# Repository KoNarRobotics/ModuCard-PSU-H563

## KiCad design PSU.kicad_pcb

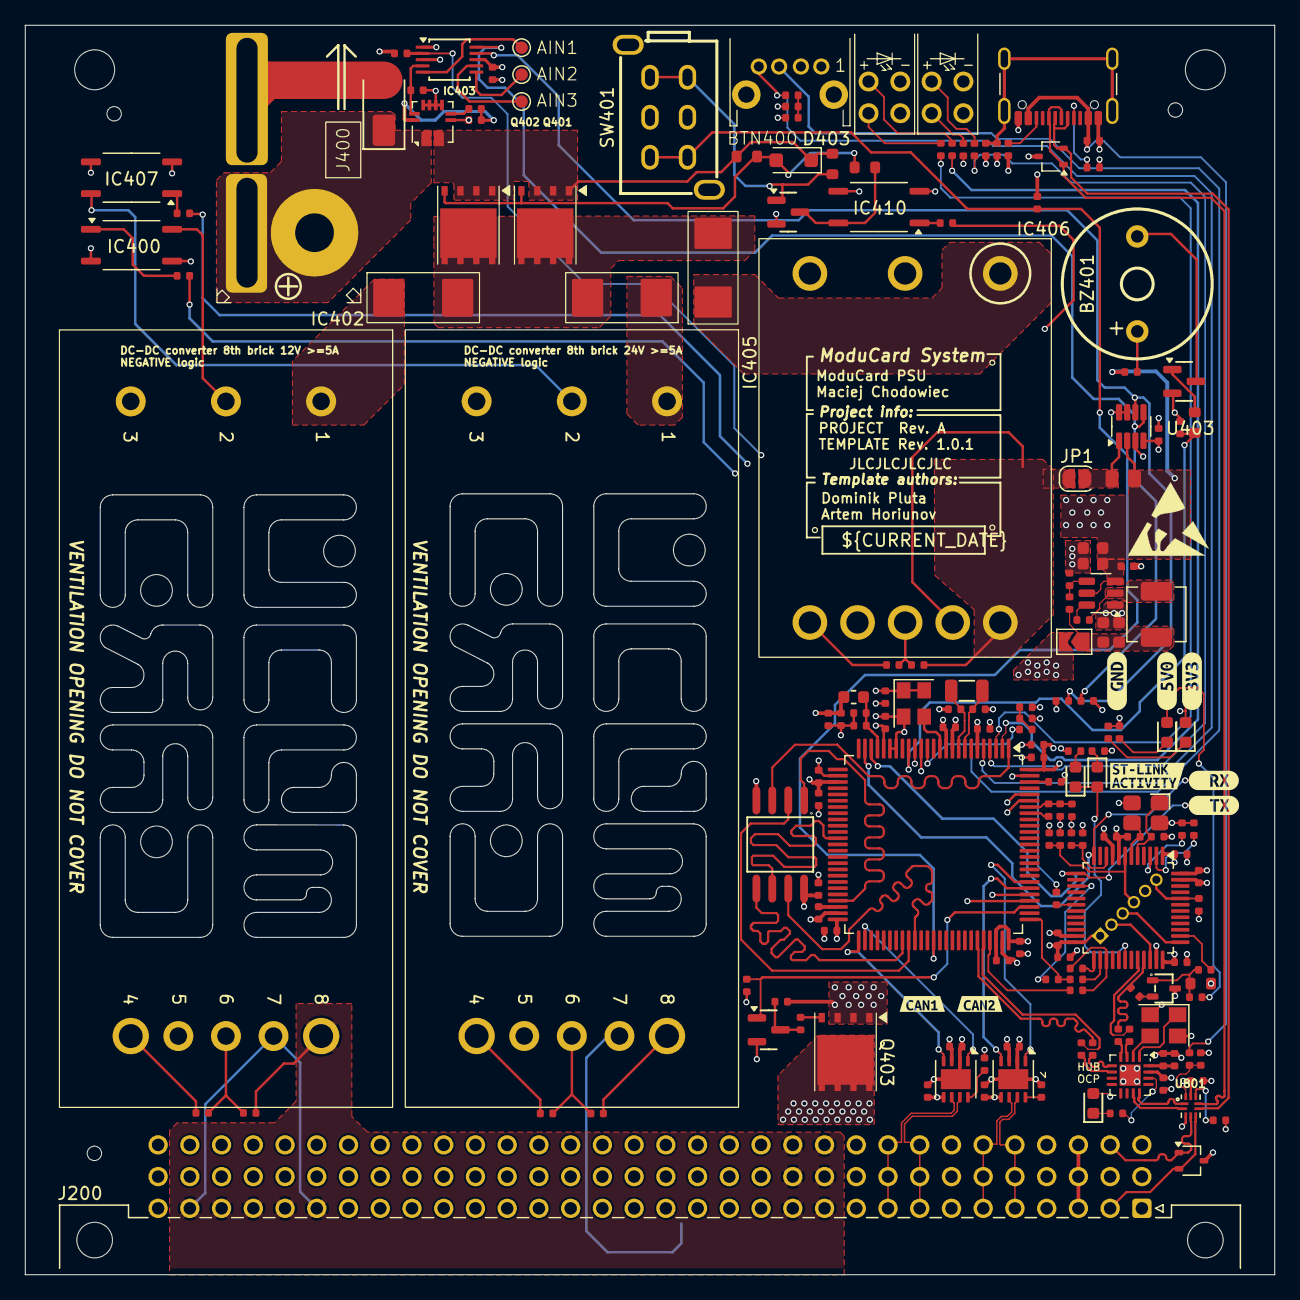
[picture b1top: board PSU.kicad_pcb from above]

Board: 4 copper layers, 100.0 x 100.0 mm, 187 parts (1 on the bottom side), 134 nets.

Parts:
BTN400: TL2243
BZ401: Buzzer; BUZ-TH_BD12.0-P7.60-D0.6-FD
C100, C306, C311, C312, C401, C402, C404, C405, C406, C417, C418, C419, C420, C421, C422, C424, C426, C428, C430, C432, C434, C500, C501, C600, C601, C701, C702, C703, C704, C705, C706, C800, C801, C900: 100nF; C_0402
C307, C308: 22uF; C_0603
C309, C310: 10uF; C_0603
C313, C314: 18pF; C_0402
C400, C403, C423, C425, C902: 10uF; C_0402
C410: 4.7uF; C_0402
C427, C429: 2.2uF; C_0402
C700, C904: 1uF; C_0402
C707, C708: 33pF; C_0402
D301: Red; D_0603
D401, D402, D701: Green; D_0603
D403: 20V; D_SOD-123F
D404: SMAJ64A; D_SMA
D700: Blue; D_0603
F402, F403, F404: 10A; Fuse_2410_6125
FB401: FB_0603
IC400, IC407, IC410: TLP185xSE; SOIC-4_4.55x3.7mm_P2.54mm
IC402, IC405: 8th DC-DC converter
IC403: ACS71240; Allegro_QFN-12-10-1EP_3x3mm_P0.5mm
IC406: 16th DC-DC converter
J200: 09031967921; DIN41612_R_3x32_Female_Horizontal_THT
J400: XT60-Angled-F; XT60-RightAngle-Adapter
J401: Conn_01x06_Pin; PinHeader_1x06_P1.27mm_Vertical
J800: USB_C_Receptacle_USB2.0_16P; USB_C_Receptacle_GCT_USB4105-xx-A_16P_TopMnt_Horizontal
JP1: Solder Jumper; SolderJumper-2_P1.3mm_Open_RoundedPad1.0x1.5mm
JP301: Test Buck Vout; SolderJumper-2_P1.3mm_Open_TrianglePad1.0x1.5mm
L301: 3.3uH; L_Changjiang_FXL0420
LED300, LED301: FixLed307
Q400, Q404: AO3400A; Q_SOT-23
Q401, Q402, Q403: HSBA8119; DFN5060-8L
Q405: MMBT5551; Q_SOT-23
Q700: MMST3904; Q_SOT-323
R306: 33k2; R_0402
R307, R401, R402, R410, R422, R423, R428, R429, R434, R435, R439, R500, R600, R701, R703, R705, R706, R707, R709, R713, R802, R804: 10kΩ; R_0402
R308, R413, R418, R437: 1kΩ; R_0402
R400: 15kΩ; R_0603
R403: 100kΩ; R_0603
R404: 36kΩ; R_0603
R411: 470Ω; R_0402
R412, R417, R440, R441, R442, R443: 220Ω; R_0402
R414, R700, R702: 100kΩ; R_0402
R415: 5.1kΩ; R_0603
R416: 100Ω; R_0603
R419: 8mΩ; R_0805
R420, R421, R424, R425, R426, R427: R; R_0402
R430, R704, R708, R715, R716, R900, R901, R902, R903: 22Ω; R_0402
R436, R438, R710, R714: 100Ω; R_0402
R445: 120Ω; R_0402
R712: 1.5kΩ; R_0402
R800, R801: 5.1kΩ; R_0402
R803: 22kΩ; R_0402
R805: 330Ω; R_0402
SW401: SW-TH_G-SWITCH-PS-22F03N
TP302, TP400, TP401, TP402, TP700, TP701: TestPoint; TestPoint_Pad_D1.0mm
U100: W25Q128; SOIC-8_L5.3-W5.3-P1.27-LS8.0-BL
U301: TPS563201DDCR; SOT-23-6
U302: CH334P; QFN-16-1EP_3x3mm_P0.5mm_EP1.7x1.7mm
U401, U402: TPD2E2U06DCK; SOT-323_SC-70
U403: INA219AIDCNR; SOT-23-8
U404: ADS1115IDGS; TSSOP-10_3x3mm_P0.5mm
U405: STM32H562VGTx; LQFP-100_14x14mm_P0.5mm
U500, U600: TJA1044GTK_3Z; HVSON-8-1EP_3x3mm_P0.65mm_EP1.6x2.4mm
U700: STM32F103CBTx; LQFP-48_7x7mm_P0.5mm
U801: FSUSB42UMX; UFQFN-10_1.4x1.8
X300: Q13FC1350000400; FC-135R_L3.2-W1.5
Y400: ASE-xxxMHz; Oscillator_SMD_Abracon_ASE-4Pin_3.2x2.5mm
Y700: 8 MHz; CRYSTAL-SMD_4P-L3.2-W2.5-BL
Y900: 12Mhz; Crystal_SMD_3225-4Pin_3.2x2.5mm
kibuzzard-67B20BD5: G***; kibuzzard-67B20BD5
kibuzzard-67B219C6: G***; kibuzzard-67B219C6
kibuzzard-67B643DE: G***; kibuzzard-67B643DE
kibuzzard-67B643EE: G***; kibuzzard-67B643EE
kibuzzard-67B2198C: G***; kibuzzard-67B2198C
kibuzzard-67B37005: G***; kibuzzard-67B37005
kibuzzard-67B37472: G***; kibuzzard-67B37472
kibuzzard-67E7D86B: G***; kibuzzard-67E7D86B

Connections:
+3V3: C100.1, C312.1, C400.1, C401.1, C402.1, C403.1, C404.1, C405.1, C406.1, C418.2, C420.1, C421.1, C422.1, C425.1, C426.1, C430.2, C432.1, C434.1, C501.1, C601.1, C700.1, C701.1, C702.1, C703.1, C704.1, C705.1, D402.2, FB401.2, IC403.10 (VCC), J401.1, JP301.2 (B), Q700.3 (C), R401.2, R410.1, R414.1, R422.1, R423.1, R434.1, R435.1, R440.1, R700.1, R701.1, R707.1, TP302.1, U100.8 (VCC), U403.4 (VS), U404.8 (VDD), U405.6 (VBAT), U405.11 (VDD), U405.21 (VREF+), U405.28 (VDD), U405.50 (VDD), U405.73 (VDDUSB), U405.75 (VDD), U405.100 (VDD), U500.5 (VIO), U600.5 (VIO), U700.1 (VBAT), U700.9 (VDDA), U700.24 (VDD), U700.36 (VDD), U700.48 (VDD), U801.9 (VCC), Y400.1 (EN), Y400.4 (Vdd)
+5V: C309.1, C310.1, C311.2, C500.2, C600.2, C904.1, D301.2, D401.2, Q403.1, Q403.2, Q403.3, R419.2, R428.1, R445.1, R709.1, U301.3 (VIN), U301.5 (EN), U302.15 (5V), U403.2 (IN-), U500.3 (VCC), U600.3 (VCC)
+5V_STDBY: J200.a3, J200.b3, J200.c3, Q403.5, Q403.6, Q403.7, Q403.8, Q403.9
+12V: IC402.7 (SENSE(+)), IC402.8 (Vout(+)), J200.a11, J200.a12, J200.a27, J200.a28, J200.a29, J200.a30, J200.a31, J200.b11, J200.b12, J200.c11, J200.c12, R424.1
+24V: IC405.7 (SENSE(+)), IC405.8 (Vout(+)), J200.a14, J200.a16, J200.a17, J200.b14, J200.c14, R426.1
/5V converter + sensor/BATTERY_FUSED: F404.1, IC406.1 (Vin(+))
/5V converter + sensor/I2C.SCL: R422.2, U403.5 (SCL), U404.10 (SCL), U405.95 (PB8)
/5V converter + sensor/I2C.SDA: R423.2, U403.6 (SDA), U404.9 (SDA), U405.96 (PB9)
/5V converter + sensor/PawełJumper: JP1.2 (B), R419.1, U403.1 (IN+)
/5V converter + sensor/PreJumper: IC406.7 (SENSE(+)), IC406.8 (Vout(+)), JP1.1 (A), R420.2
/5V converter + sensor/TRIM: IC406.6 (TRIM), R420.1, R421.2
/12V conveter + sensor/BATTERY: F402.2, F403.2, F404.2, Q401.5, Q401.6, Q401.7, Q401.8, Q401.9, Q402.5, Q402.6, Q402.7, Q402.8, Q402.9
/12V conveter + sensor/FUSE: F402.1, IC402.1 (Vin(+))
/12V conveter + sensor/ON-OFF0: Q400.1 (G), R429.1, U405.78 (PC10)
/12V conveter + sensor/ON-OFF1: R413.2, U405.79 (PC11)
/12V conveter + sensor/ON-OFF2: R418.2, U405.80 (PC12)
/12V conveter + sensor/ON/OFF: IC400.6, IC402.2 (ON/OFF)
/12V conveter + sensor/TRIM: IC402.6 (TRIM), R424.2, R425.2
/??V converter + sensor/FUSE: F403.1, IC405.1 (Vin(+))
/??V converter + sensor/ON/OFF: IC405.2 (ON/OFF), IC407.6
/??V converter + sensor/TRIM: IC405.6 (TRIM), R426.2, R427.2
/Backplane/BACKPLANE.D+: J200.a2, U402.2, U801.5 (HSD1+)
/Backplane/BACKPLANE.D-: J200.c2, U402.1, U801.4 (HSD1-)
/Backplane/CAN1.+: J200.a5, J200.b5, J200.c5, U500.7 (CANH)
/Backplane/CAN1.-: J200.a6, J200.b6, J200.c6, U500.6 (CANL)
/Backplane/CAN2.+: J200.a8, J200.b8, J200.c8, U600.7 (CANH)
/Backplane/CAN2.-: J200.a9, J200.b9, J200.c9, U600.6 (CANL)
/Battery connector/ADS115/RDY: R410.2, U404.2 (ALERT/RDY), U405.16 (PC1)
/Battery connector/MASTER_ON: R417.2, U405.15 (PC0)
/Battery connector/VIOUT: C428.2, IC403.9 (VIOUT), U404.4 (AIN0)
/CAN transceiver 1/CAN.RX: U405.81 (PD0), U500.4 (RXD)
/CAN transceiver 1/CAN.TX: U405.82 (PD1), U500.1 (TXD)
/CAN transceiver 2/CAN.RX: U405.51 (PB12), U600.4 (RXD)
/CAN transceiver 2/CAN.TX: U405.52 (PB13), U600.1 (TXD)
/MCU/BOOT0: C410.1, R437.2, R439.1, U405.94 (BOOT0)
/MCU/BOOT_EN: R437.1, U405.93 (PB7)
/MCU/Buzzer: R402.1, R416.1, U405.17 (PC2)
/MCU/NRST: C419.1, R435.2, R436.1
/MCU/OSC32_IN: C314.1, U405.8 (PC14), X300.2
/MCU/OSC32_OUT: C313.1, U405.9 (PC15), X300.1
/MCU/OSC_IN: U405.12 (PH0), Y400.3 (OUT)
/MCU/Power_Button_IN: R401.1, SW401.1 (NO), SW401.4 (NO), U405.63 (PC6)
/MCU/QSPI1.CS: U100.1 (CS#), U405.47 (PB10)
/MCU/QSPI1.IO0: U100.5 (DI), U405.58 (PD11)
/MCU/QSPI1.IO1: U100.2 (DO), U405.59 (PD12)
/MCU/QSPI1.IO2: U100.3 (IO2), U405.1 (PE2)
/MCU/QSPI1.IO3: U100.7 (IO3), U405.60 (PD13)
/MCU/QSPI1.SCLK: U100.6 (CLK), U405.37 (PB2)
/MCU/STATUS_LED: R441.1, U405.4 (PE5)
/MCU/STLINK.RX: TP701.1, U405.23 (PA0), U700.13 (PA3)
/MCU/STLINK.TX: TP700.1, U405.24 (PA1), U700.12 (PA2)
/MCU/SWD.SWCLK: R704.2, R715.1, U405.76 (PA14(JTCK)
/MCU/SWD.SWDIO: R716.1, U405.72 (PA13(JTMS)
/MCU/SWD.~RST: BTN400.3, R436.2, R708.1, U405.14 (NRST)
/MCU/USB_MCU.D+: R901.1, U405.71 (PA12)
/MCU/USB_MCU.D-: R900.1, U405.70 (PA11)
/MCU/USER_LED_1: R442.1, U405.2 (PE3)
/MCU/USER_LED_2: R443.1, U405.3 (PE4)
/MCU/USR_BTN: C417.1, R434.2, R438.1
/MCU/USR_BUTTON: BTN400.4, R438.2, U405.5 (PE6)
/MCU/VCAP_1: C427.1, U405.48 (VCAP)
/MCU/VCAP_2: C429.1, U405.98 (VCAP)
/MCU/VDDA: C423.1, C424.1, FB401.1, U405.22 (VDDA)
/Power/+3V3_UNPROTEC: C307.1, C308.1, JP301.1 (A), L301.2, R306.1
/Power/FB_3V3: R306.2, R307.1, U301.4 (VFB)
/Power/SW_3V3: C306.2, L301.1, U301.2 (SW)
/Power/VBST_3V3: C306.1, U301.6 (VBST)
/ST-LINK/CLK: J401.3, U700.37 (PA14)
/ST-LINK/DIO: J401.2, U700.34 (PA13)
/ST-LINK/LED: D700.1, D701.2, U700.30 (PA9)
/ST-LINK/ST-LINK.D+: R712.2, R903.1, U700.33 (PA12)
/ST-LINK/ST-LINK.D-: R902.1, U700.32 (PA11)
/ST-LINK/STLINK-BOOT0: J401.6, R702.2, U700.44 (BOOT0)
/ST-LINK/STLINK-OSC_IN: C707.1, U700.5 (PD0), Y700.1
/ST-LINK/STLINK-OSC_OUT: C708.1, U700.6 (PD1), Y700.3
/ST-LINK/STLINK-RST: C706.1, J401.4, R700.2, U700.7 (NRST)
/ST-LINK/USB_RENUM: R710.2, U700.38 (PA15)
/USB-hub/USBIN1.D+: U302.12 (DPU), U801.1 (D+)
/USB-hub/USBIN1.D-: U302.11 (DMU), U801.2 (D-)
/USB-hub/USBOUT1_R.D+: R903.2, U302.4 (DP4)
/USB-hub/USBOUT1_R.D-: R902.2, U302.3 (DM4)
/USB-hub/USB_MCU_R.D+: R901.2, U302.6 (DP3)
/USB-hub/USB_MCU_R.D-: R900.2, U302.5 (DM3)
/USB/CC1: J800.A5 (CC1), R801.1
/USB/CC2: J800.B5 (CC2), R800.1
/USB/USB2S.D+: J800.A6 (D+), J800.B6 (D+), U401.1, U801.7 (HSD2+)
/USB/USB2S.D-: J800.A7 (D-), J800.B7 (D-), U401.2, U801.6 (HSD2-)
/USB/VBUS_IN: C800.1, J800.A4 (VBUS), J800.A9 (VBUS), J800.B4 (VBUS), J800.B9 (VBUS), R802.1
GND: BTN400.1, BTN400.2, C100.2, C307.2, C308.2, C309.2, C310.2, C311.1, C312.2, C313.2, C314.2, C400.2, C401.2, C402.2, C403.2, C404.2, C405.2, C406.2, C410.2, C417.2, C418.1, C419.2, C420.2, C421.2, C422.2, C423.2, C424.2, C425.2, C426.2, C427.2, C428.1, C429.2, C430.1, C432.2, C434.2, C500.1, C501.2, C600.1, C601.2, C700.2, C701.2, C702.2, C703.2, C704.2, C705.2, C706.2, C707.2, C708.2, C800.2, C801.2, C900.2, C902.2, C904.2, D404.2, IC400.3, IC400.4, IC402.3 (Vin(-)), IC402.4 (Vout(-)), IC402.5 (SENSE(-)), IC403.3 (GND), IC403.5 (NC), IC403.6 (NC), IC403.7 (NC), IC403.8 (NC), IC405.3 (Vin(-)), IC405.4 (Vout(-)), IC405.5 (SENSE(-)), IC406.2 (ON/OFF), IC406.3 (Vin(-)), IC406.4 (Vout(-)), IC406.5 (SENSE(-)), IC407.3, IC407.4, IC410.3, IC410.4, J200.a1, J200.a4, J200.a7, J200.a10, J200.a13, J200.a15, J200.a18, J200.a19, J200.a20, J200.a21, J200.a22, J200.a23, J200.a24, J200.a25, J200.a26, J200.a32, J200.b1, J200.b2, J200.b4, J200.b7, J200.b10, J200.b13, J200.b15, J200.b32, J200.c1, J200.c4, J200.c7, J200.c10, J200.c13, J200.c15, J200.c32, J400.2 (GND), J401.5, J800.A1 (GND), J800.A12 (GND), J800.B1 (GND), J800.B12 (GND), LED300.2, LED300.4, LED301.2, LED301.4, Q400.2 (S), Q404.2 (S), Q405.2 (E), R307.2, R402.2, R404.2, R411.2, R412.2, R421.1, R425.1, R427.1, R429.2, R439.2, R500.2, R600.2, R702.1, R703.2, R705.1, R706.1, R713.2, R800.2, R801.2, R803.2, R804.2, R805.2, SW401.2 (COM), SW401.5 (COM), SW401.7 (SHLD), SW401.8 (SHLD), U100.4 (GND), U301.1 (GND), U302.17 (GND), U401.3, U402.3, U403.3 (GND), U403.7 (A0), U403.8 (A1), U404.1 (ADDR), U404.3 (GND), U405.10 (VSS), U405.19 (VSSA), U405.20 (VREF-), U405.27 (VSS), U405.49 (VSS), U405.74 (VSS), U405.99 (VSS), U500.2 (GND), U500.9 (EP), U600.2 (GND), U600.9 (EP), U700.8 (VSSA), U700.23 (VSS), U700.35 (VSS), U700.47 (VSS), U801.3 (GND), Y400.2 (GND), Y700.2, Y700.4, Y900.2, Y900.4
unnamed: BZ401.1 (+), R445.2
unnamed: BZ401.2 (-), Q404.3 (D)
unnamed: D301.1, R308.2
unnamed: D401.1, R411.1
unnamed: D402.1, R412.1
unnamed: D403.2 (A), Q401.4, Q402.4, R400.1, R415.2
unnamed: D403.1 (K), IC403.2 (IP–), Q401.1, Q401.2, Q401.3, Q402.1, Q402.2, Q402.3, R403.1, R415.1
unnamed: D700.2, R707.2
unnamed: D701.1, R713.1
unnamed: IC400.1, R413.1
unnamed: D404.1, IC403.1 (IP+), J400.1 (PWR)
unnamed: IC403.4 (~FAULT), R414.2
unnamed: IC407.1, R418.1
unnamed: IC410.1, R417.1
unnamed: C801.1, J800.S1 (SHIELD), R805.1
unnamed: LED300.1, R442.2
unnamed: LED300.3, R443.2
unnamed: LED301.1, R441.2
unnamed: LED301.3, R440.2
unnamed: Q400.3 (D), R428.2, R430.1
unnamed: Q403.4, R430.2
unnamed: Q404.1 (G), R416.2
unnamed: Q405.1 (B), R403.2, SW401.3 (NC), SW401.6 (NC)
unnamed: IC410.6, Q405.3 (C), R400.2
unnamed: Q700.1 (B), R404.1, R709.2, R710.1
unnamed: Q700.2 (E), R712.1
unnamed: C900.1, C902.1, U302.16 (3V3)
unnamed: R308.1, U302.14 (PGANG)
unnamed: U302.2 (XI), Y900.3
unnamed: U302.1 (XO), Y900.1
unnamed: TP400.1, U404.5 (AIN1)
unnamed: TP401.1, U404.6 (AIN2)
unnamed: TP402.1, U404.7 (AIN3)
unnamed: R500.1, U500.8 (STB)
unnamed: R600.1, U600.8 (STB)
unnamed: R701.2, R703.1, U700.10 (PA0)
unnamed: R704.1, U700.15 (PA5)
unnamed: R708.2, U700.18 (PB0)
unnamed: R714.2, U700.25 (PB12)
unnamed: R715.2, U700.26 (PB13)
unnamed: R714.1, R716.2, U700.27 (PB14)
unnamed: R705.2, U700.2 (PC13)
unnamed: R706.2, U700.3 (PC14)
unnamed: R802.2, R803.1, U801.10 (SEL)
unnamed: R804.1, U801.8 (~OE)

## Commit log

2025-09-30 Change MCU to STM32H563
2025-09-30 Add LCSC numbers
2025-09-30 Create production files
2025-11-06 layout done
